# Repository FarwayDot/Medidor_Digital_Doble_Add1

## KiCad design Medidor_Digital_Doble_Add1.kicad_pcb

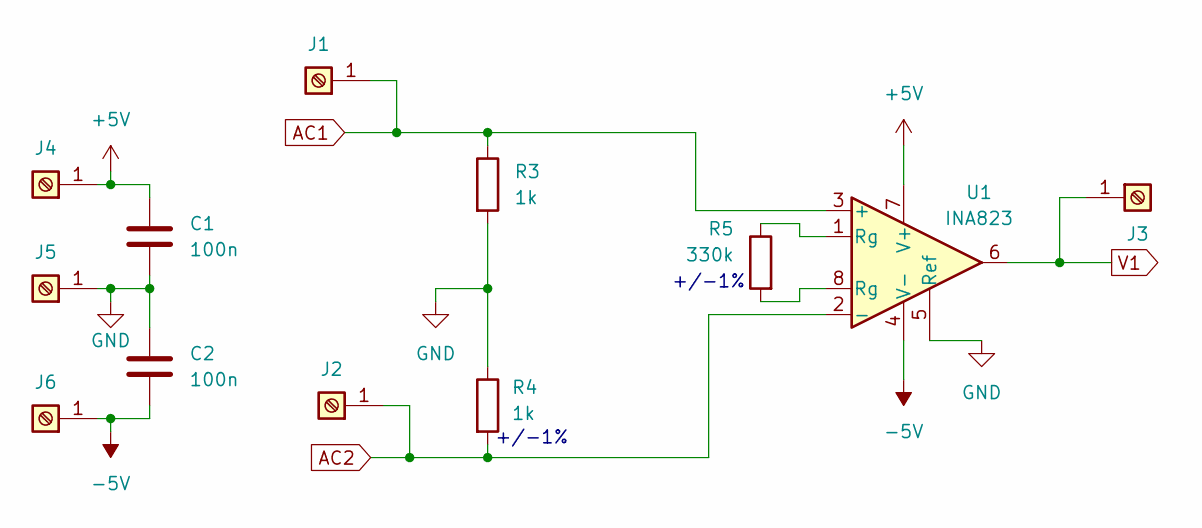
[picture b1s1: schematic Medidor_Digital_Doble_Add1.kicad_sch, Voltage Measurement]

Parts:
C1, C2: 100n; C_0805_2012Metric
J1, J2, J3, J4, J5, J6: Screw_Terminal_01x01; PAD_2.54_1.0
R3, R4: 1k; R_0805_2012Metric
R5: 330k; R_0805_2012Metric
U1: INA823; SOIC-8_3.9x4.9mm_P1.27mm

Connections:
+5V: C1.1, J4.1, U1.7 (V+)
-5V: C2.2, J6.1, U1.4 (V-)
AC1: J1.1, R3.1, U1.3 (+)
AC2: J2.1, R4.2, U1.2 (-)
GND: C1.2, C2.1, J5.1, R3.2, R4.1, U1.5 (Ref)
unnamed: R5.1, U1.1 (Rg)
unnamed: R5.2, U1.8 (Rg)
V1: J3.1, U1.6

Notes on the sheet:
+/-1%

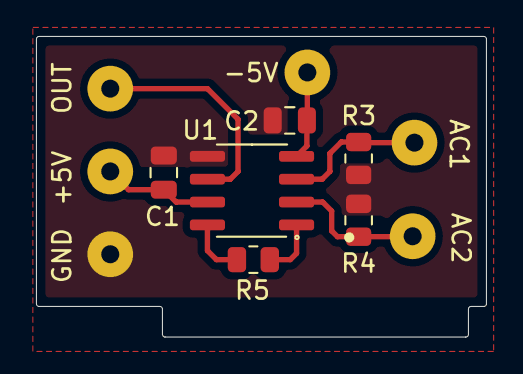
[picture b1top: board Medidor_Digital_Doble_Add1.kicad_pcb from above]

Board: 2 copper layers, 25.0 x 16.7 mm, 12 parts (0 on the bottom side), 8 nets.

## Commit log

2024-05-25 Adaptación para el medidor digital. Su función es la de mejorar la medición de voltaje en el medidor digital doble
2024-05-25 Se termina el PCB, pero se requiere una PCB de menor tamaño y a una cara.
2024-05-25 SCH:Se cambia la resistencia de 1.2k a 1k. PCB:Se rediseña la distribución para menor altura de la placa.
